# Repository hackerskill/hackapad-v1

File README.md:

# hackapad-v1
A macropad! V1 of it.

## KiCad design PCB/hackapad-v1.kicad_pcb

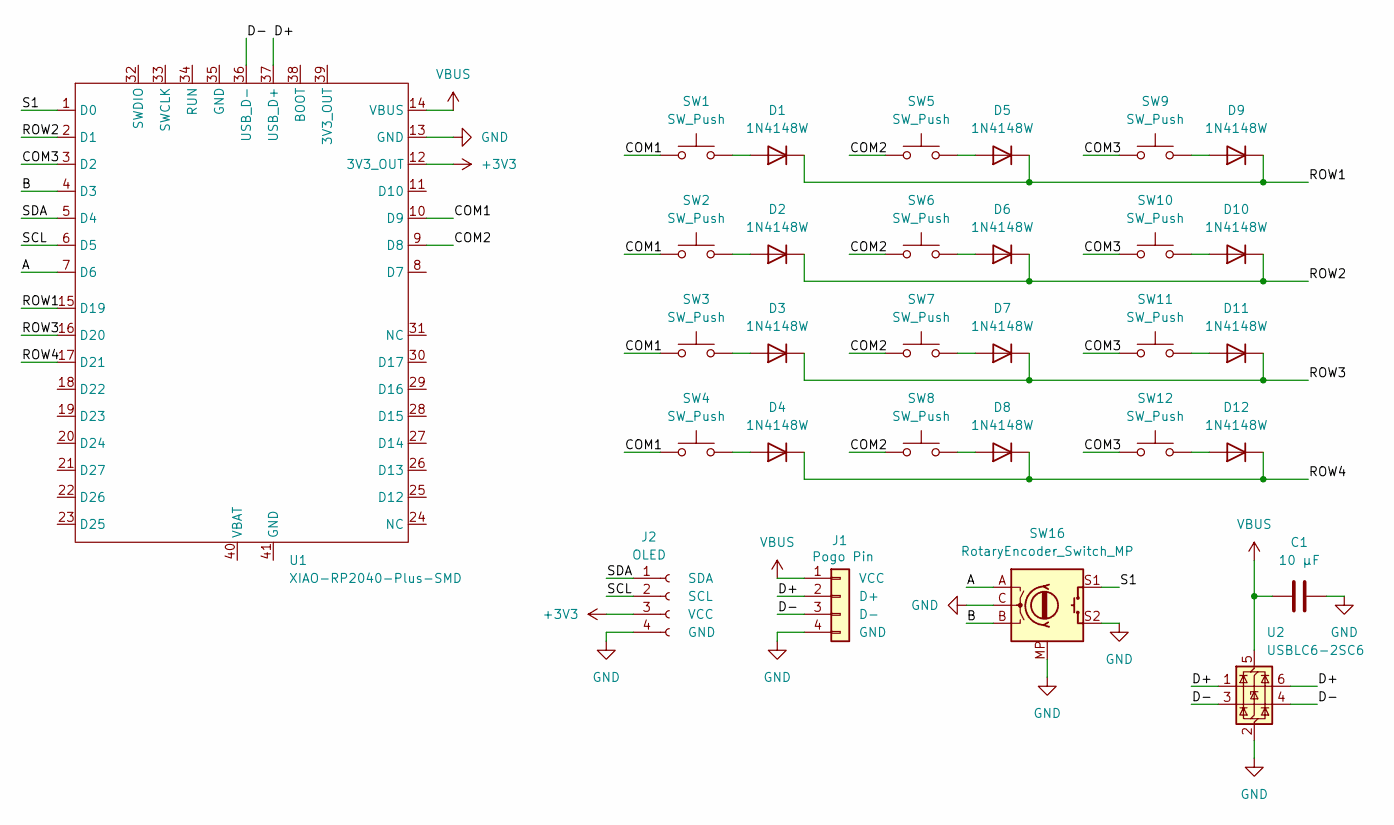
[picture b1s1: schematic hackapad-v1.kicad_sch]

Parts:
C1: 10 µF; C_0805_2012Metric_Pad1.18x1.45mm_HandSolder
D1, D2, D3, D4, D5, D6, D7, D8, D9, D10, D11, D12: 1N4148W; D_SOD-123
J1: Pogo Pin; PinHeader_1x04_P2.54mm_Vertical
J2: OLED; PinSocket_1x04_P2.54mm_Vertical
SW1, SW2, SW3, SW4, SW5, SW6, SW7, SW8, SW9, SW10, SW11, SW12: SW_Push; SW_Cherry_MX_1.00u_PCB
SW16: RotaryEncoder_Switch_MP; RotaryEncoder_Alps_EC11E-Switch_Vertical_H20mm
U1: XIAO-RP2040-Plus-SMD
U2: USBLC6-2SC6; SOT-23-6_Handsoldering

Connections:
+3V3: J2.3 (VCC), U1.12 (3V3_OUT)
/A: SW16.A, U1.7 (D6)
/B: SW16.B, U1.4 (D3)
/COM1: SW1.1, SW2.1, SW3.1, SW4.1, U1.10 (D9)
/COM2: SW5.1, SW6.1, SW7.1, SW8.1, U1.9 (D8)
/COM3: SW9.1, SW10.1, SW11.1, SW12.1, U1.3 (D2)
/D+: J1.2 (D+), U1.37 (USB_D+), U2.1 (I/O1), U2.6 (I/O1)
/D-: J1.3 (D-), U1.36 (USB_D-), U2.3 (I/O2), U2.4 (I/O2)
/ROW1: D1.1 (K), D5.1 (K), D9.1 (K), U1.15 (D19)
/ROW2: D2.1 (K), D6.1 (K), D10.1 (K), U1.2 (D1)
/ROW3: D3.1 (K), D7.1 (K), D11.1 (K), U1.16 (D20)
/ROW4: D4.1 (K), D8.1 (K), D12.1 (K), U1.17 (D21)
/S1: SW16.S1, U1.1 (D0)
/SCL: J2.2 (SCL), U1.6 (D5)
/SDA: J2.1 (SDA), U1.5 (D4)
GND: C1.1, J1.4 (GND), J2.4 (GND), SW16.C, SW16.MP, SW16.S2, U1.13 (GND), U2.2 (GND)
unnamed: D1.2 (A), SW1.2
unnamed: D2.2 (A), SW2.2
unnamed: D3.2 (A), SW3.2
unnamed: D4.2 (A), SW4.2
unnamed: D5.2 (A), SW5.2
unnamed: D6.2 (A), SW6.2
unnamed: D7.2 (A), SW7.2
unnamed: D8.2 (A), SW8.2
unnamed: D9.2 (A), SW9.2
unnamed: D10.2 (A), SW10.2
unnamed: D11.2 (A), SW11.2
unnamed: D12.2 (A), SW12.2
VBUS: C1.2, J1.1 (VCC), U1.14 (VBUS), U2.5 (VBUS)

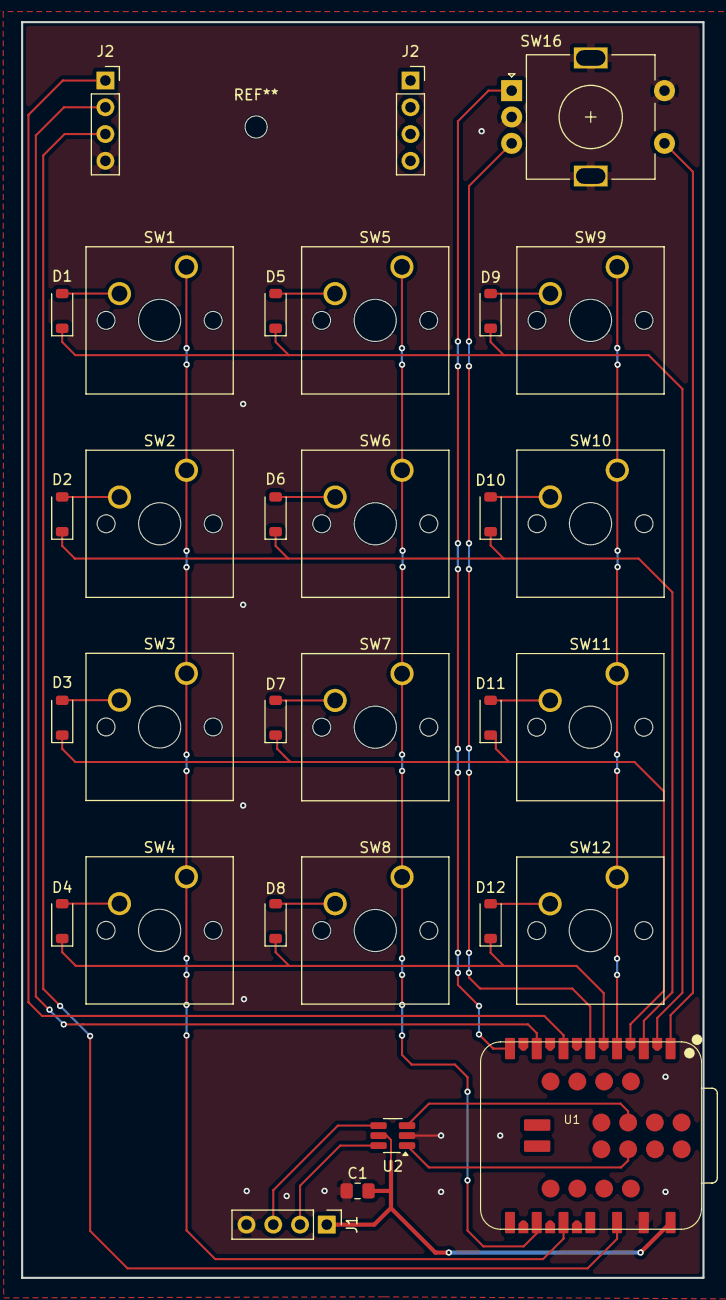
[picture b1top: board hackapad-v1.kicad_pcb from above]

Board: 2 copper layers, 64.7 x 119.2 mm, 31 parts (0 on the bottom side), 29 nets.

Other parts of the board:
J2#2: OLED; PinSocket_1x04_P2.54mm_Vertical
